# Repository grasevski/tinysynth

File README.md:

# tinysynth
Attiny25 "passive" midi to audio converter

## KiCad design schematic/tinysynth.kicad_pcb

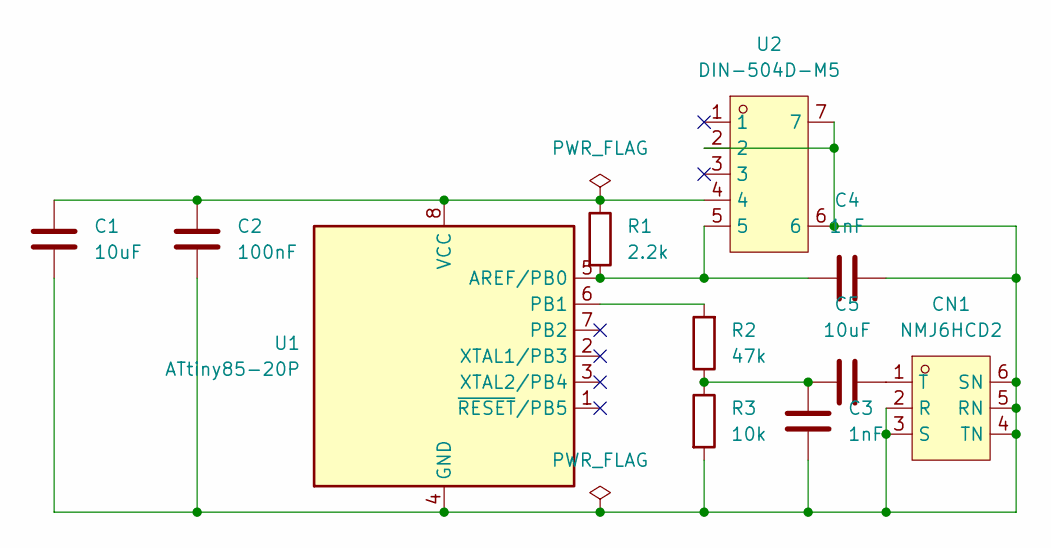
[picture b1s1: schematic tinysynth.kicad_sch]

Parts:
C1, C5: 10uF; C_1206_3216Metric
C2: 100nF; C_1206_3216Metric
C3, C4: 1nF; C_1206_3216Metric
CN1: NMJ6HCD2; AUDIO-TH_NMJ6HCD2; LCSC Part C368502
R1: 2.2k; R_1206_3216Metric
R2: 47k; R_1206_3216Metric
R3: 10k; R_1206_3216Metric
U1: ATtiny85-20P; DIP-8_W7.62mm_Socket
U2: DIN-504D-M5; CONN-TH_DIN-504D-M5; LCSC Part C2939347

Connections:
unnamed: C3.1, C5.1, R2.1, R3.1
unnamed: C1.2, C2.2, C3.2, C4.2, CN1.2 (R), CN1.3 (S), CN1.4 (TN), CN1.5 (RN), CN1.6 (SN), R3.2, U1.4 (GND), U2.2, U2.6, U2.7
unnamed: C5.2, CN1.1 (T)
unnamed: C4.1, R1.2, U1.5 (AREF/PB0), U2.5
unnamed: R2.2, U1.6 (PB1)
unnamed: C1.1, C2.1, R1.1, U1.8 (VCC), U2.4

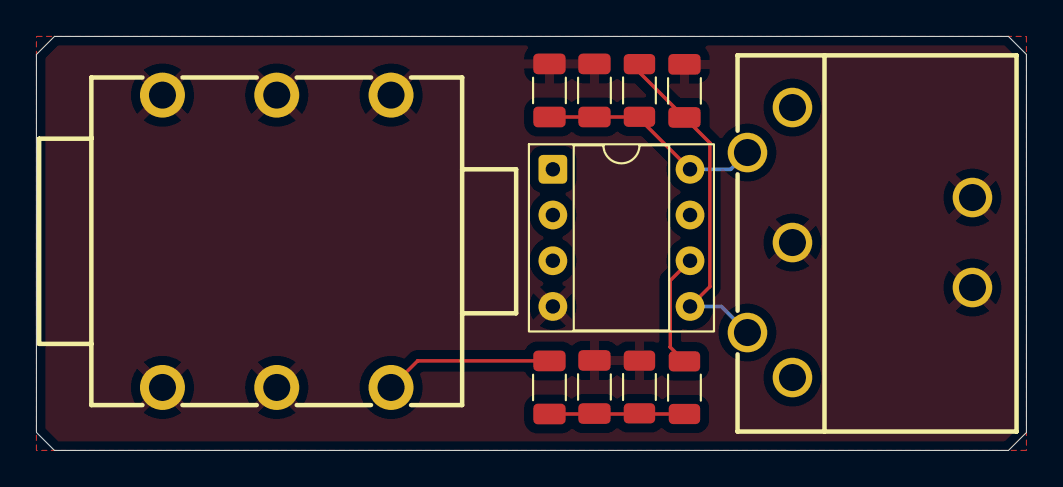
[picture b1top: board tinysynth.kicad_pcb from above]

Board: 2 copper layers, 55.0 x 23.0 mm, 11 parts (0 on the bottom side), 6 nets.

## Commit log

2026-02-18 feat(pcb): first draft
    This change adds the kicad schematic for a pcb with connectors on one
    side and smt components on the other side.
2026-02-19 feat(pcb): done pcb as well as enclosure
    Only thing left is the actual code.
2026-03-29 about to increase to 8 voices
2026-05-27 did attiny25 socket version
